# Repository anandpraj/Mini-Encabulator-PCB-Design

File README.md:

# Mini-Encabulator-PCB-Design
This simple device only does two things: 
● Blinks an LED when the user holds down a button. 
● Sets blink rate proportional to potentiometer position.

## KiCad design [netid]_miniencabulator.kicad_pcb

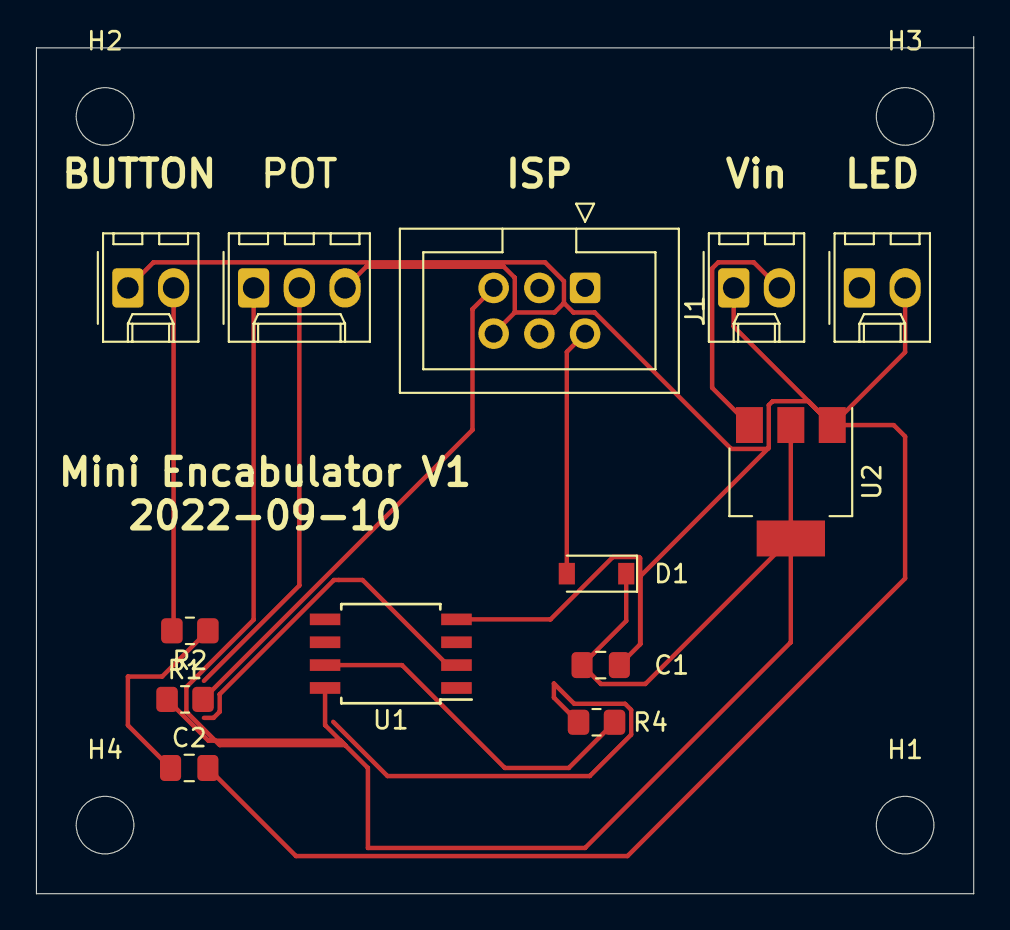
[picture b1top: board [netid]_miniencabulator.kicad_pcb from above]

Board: 2 copper layers, 52.1 x 47.6 mm, 17 parts (0 on the bottom side), 10 nets.

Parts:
C1, C2: 1 µF; C_0805_2012Metric_Pad1.18x1.45mm_HandSolder
D1: MBR0520; D_SOD-123
H1, H2, H3, H4: MountingHole; MountingHole_3.2mm_M3
J1: AVR-ISP-6; IDC-Header_2x03_P2.54mm_Vertical
J2: Vin; Molex_KK-254_AE-6410-02A_1x02_P2.54mm_Vertical
J3: BUTTON; Molex_KK-254_AE-6410-02A_1x02_P2.54mm_Vertical
J4: LED; Molex_KK-254_AE-6410-02A_1x02_P2.54mm_Vertical
J5: POT; Molex_KK-254_AE-6410-03A_1x03_P2.54mm_Vertical
R1, R2: 10k; R_0805_2012Metric_Pad1.20x1.40mm_HandSolder
R4: 1k; R_0805_2012Metric_Pad1.20x1.40mm_HandSolder
U1: ATtiny85-20SU; SOIJ-8_5.3x5.3mm_P1.27mm
U2: LM1117-5.0; SOT-223-3_TabPin2

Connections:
+5V: C1.1, D1.1, J5.1, R1.1, U1.8, U2.2
GND: C1.2, C2.2, J1.6, J2.1, J3.1, J4.2, J5.3, U1.4, U2.1
unnamed: C2.1, R2.1
unnamed: D1.2, J1.2
unnamed: J1.5, R1.2
unnamed: J2.2, U2.3
unnamed: J3.2, R2.2
unnamed: J4.1, R4.1
unnamed: J5.2, U1.2
unnamed: R4.2, U1.7
